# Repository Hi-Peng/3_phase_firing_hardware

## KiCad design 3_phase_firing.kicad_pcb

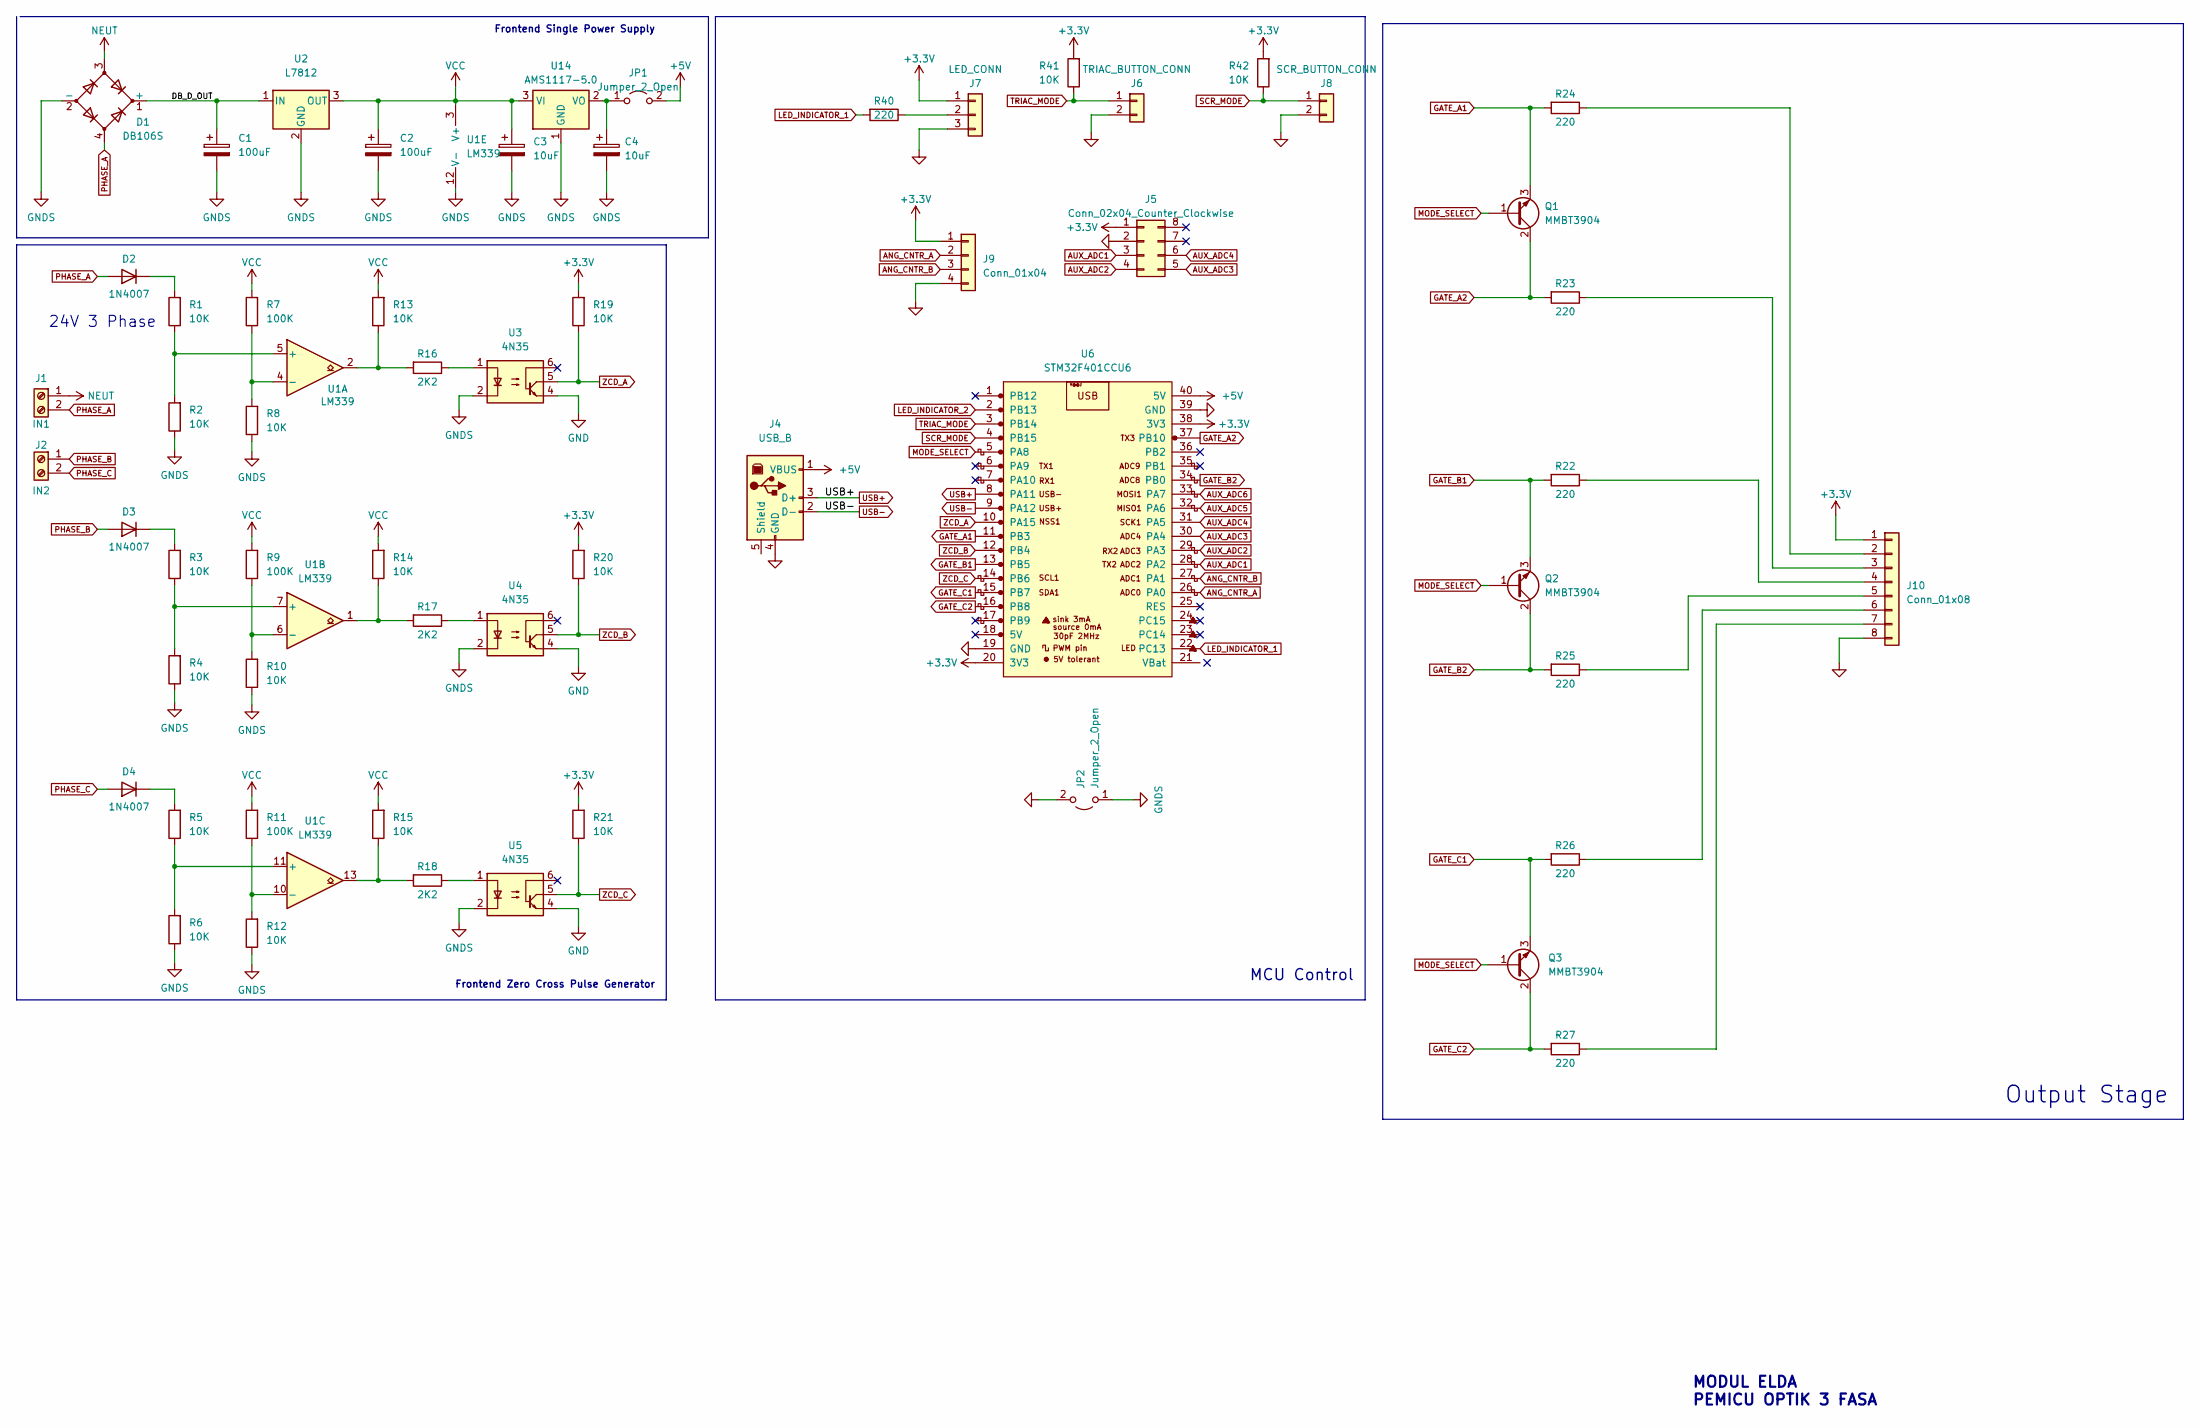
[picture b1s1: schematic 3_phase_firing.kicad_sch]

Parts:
C1, C2: 100uF; CP_Elec_6.3x7.7
C3, C4: 10uF; CP_Elec_6.3x7.7
D1: DB106S; Diode_Bridge_OnSemi_SDIP-4L
D2, D3, D4: 1N4007; D_SMA_Handsoldering
J1: IN1; TerminalBlock_bornier-2_P5.08mm
J2: IN2; TerminalBlock_bornier-2_P5.08mm
J4: USB_B; USB_B_OST_USB-B1HSxx_Horizontal
J5: Conn_02x04_Counter_Clockwise; PinHeader_2x04_P2.54mm_Vertical
J6: TRIAC_BUTTON_CONN; JST_XH_B2B-XH-A_1x02_P2.50mm_Vertical
J7: LED_CONN; JST_XH_B3B-XH-A_1x03_P2.50mm_Vertical
J8: SCR_BUTTON_CONN; JST_XH_B2B-XH-A_1x02_P2.50mm_Vertical
J9: Conn_01x04; JST_XH_B4B-XH-A_1x04_P2.50mm_Vertical
J10: Conn_01x08; JST_XH_B8B-XH-A_1x08_P2.50mm_Vertical
JP1, JP2: Jumper_2_Open; PinHeader_1x02_P2.54mm_Vertical
Q1, Q2, Q3: MMBT3904; SOT-23
R1, R2, R3, R4, R5, R6, R8, R10, R12, R13, R14, R15, R19, R20, R21, R41, R42: 10K; R_0805_2012Metric
R7, R9, R11: 100K; R_0805_2012Metric
R16, R17, R18: 2K2; R_0805_2012Metric
R22, R23, R24, R25, R26, R27: 220; R_0805_2012Metric
R40: 220; R_1206_3216Metric_Pad1.30x1.75mm_HandSolder
U1: LM339; SOIC-14_3.9x8.7mm_P1.27mm
U2: L7812; TO-263-2
U3, U4, U5: 4N35; DIP-6_W8.89mm_SMDSocket_LongPads
U6: STM32F401CCU6; YAAJ_WeAct_BlackPill_2
U14: AMS1117-5.0; SOT-223-3_TabPin2

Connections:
+3.3V: J5.1, J7.1, J9.1, J10.1, R19.2, R20.2, R21.2, R41.2, R42.2, U6.20 (3V3), U6.38 (3V3)
+5V: J4.1 (VBUS), JP1.2 (B), U6.40 (5V)
/DB_D_OUT: C1.1, D1.1 (+), U2.1 (IN)
ANG_CNTR_A: J9.2, U6.26 (PA0)
ANG_CNTR_B: J9.3, U6.27 (PA1)
AUX_ADC1: J5.3, U6.28 (PA2)
AUX_ADC2: J5.4, U6.29 (PA3)
AUX_ADC3: J5.5, U6.30 (PA4)
AUX_ADC4: J5.6, U6.31 (PA5)
AUX_ADC5: U6.32 (PA6)
AUX_ADC6: U6.33 (PA7)
GATE_A1: Q1.3 (E), R24.2, U6.11 (PB3)
GATE_A2: Q1.2 (C), R23.2, U6.37 (PB10)
GATE_B1: Q2.3 (E), R22.2, U6.13 (PB5)
GATE_B2: Q2.2 (C), R25.2, U6.34 (PB0)
GATE_C1: Q3.3 (E), R26.2, U6.15 (PB7)
GATE_C2: Q3.2 (C), R27.2, U6.16 (PB8)
GND: J4.4 (GND), J5.2, J6.2, J7.3, J8.2, J9.4, J10.8, JP2.2 (B), U3.4, U4.4, U5.4, U6.19 (GND), U6.39 (GND)
GNDS: C1.2, C2.2, C3.2, C4.2, D1.2 (-), JP2.1 (A), R2.1, R4.1, R6.1, R8.1, R10.1, R12.1, U1.12 (V-), U2.2 (GND), U3.2, U4.2, U5.2, U14.1 (GND)
LED_INDICATOR_1: R40.2, U6.22 (PC13)
LED_INDICATOR_2: U6.2 (PB13)
MODE_SELECT: Q1.1 (B), Q2.1 (B), Q3.1 (B), U6.5 (PA8)
NEUT: D1.3, J1.1
unnamed: D2.1 (K), R1.2
unnamed: D3.1 (K), R3.2
unnamed: D4.1 (K), R5.2
unnamed: J7.2, R40.1
unnamed: J10.2, R24.1
unnamed: J10.3, R23.1
unnamed: J10.4, R22.1
unnamed: J10.5, R25.1
unnamed: J10.6, R26.1
unnamed: J10.7, R27.1
unnamed: C4.1, JP1.1 (A), U14.2 (VO)
unnamed: R13.1, R16.2, U1.2
unnamed: R14.1, R17.2, U1.1
unnamed: R15.1, R18.2, U1.13
unnamed: R16.1, U3.1
unnamed: R17.1, U4.1
unnamed: R18.1, U5.1
unnamed: R1.1, R2.2, U1.5 (+)
unnamed: R7.1, R8.2, U1.4 (-)
unnamed: R3.1, R4.2, U1.7 (+)
unnamed: R9.1, R10.2, U1.6 (-)
unnamed: R5.1, R6.2, U1.11 (+)
unnamed: R11.1, R12.2, U1.10 (-)
PHASE_A: D1.4, D2.2 (A), J1.2
PHASE_B: D3.2 (A), J2.1
PHASE_C: D4.2 (A), J2.2
SCR_MODE: J8.1, R42.1, U6.4 (PB15)
TRIAC_MODE: J6.1, R41.1, U6.3 (PB14)
USB+: J4.3 (D+), U6.8 (PA11)
USB-: J4.2 (D-), U6.9 (PA12)
VCC: C2.1, C3.1, R7.2, R9.2, R11.2, R13.2, R14.2, R15.2, U1.3 (V+), U2.3 (OUT), U14.3 (VI)
ZCD_A: R19.1, U3.5, U6.10 (PA15)
ZCD_B: R20.1, U4.5, U6.12 (PB4)
ZCD_C: R21.1, U5.5, U6.14 (PB6)

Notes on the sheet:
MODUL ELDA PEMICU OPTIK 3 FASA
Frontend Zero Cross Pulse Generator
MCU Control
Frontend Single Power Supply
24V 3 Phase
Output Stage

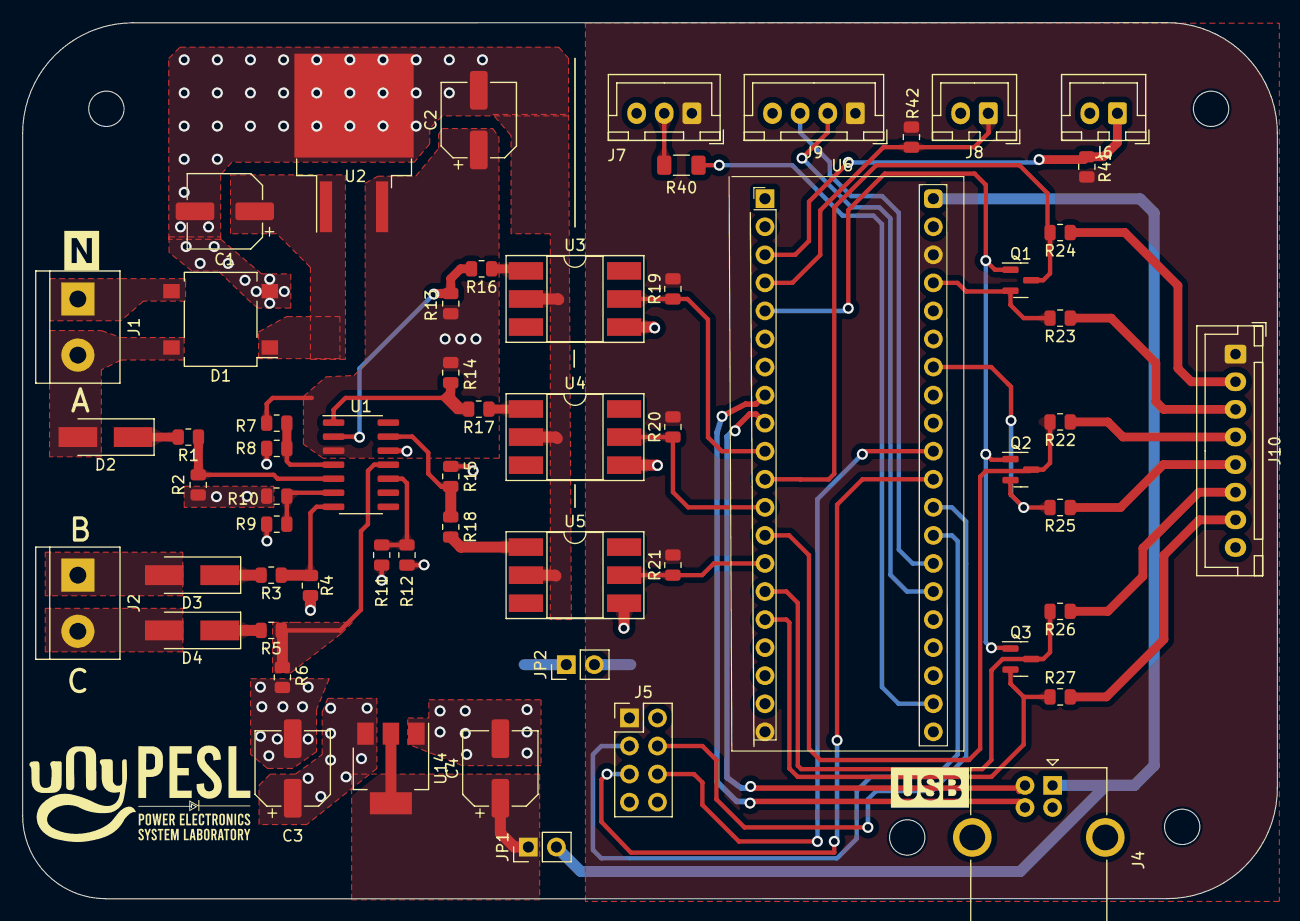
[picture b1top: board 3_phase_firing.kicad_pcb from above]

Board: 2 copper layers, 113.6 x 79.3 mm, 61 parts (0 on the bottom side), 54 nets.

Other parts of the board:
kibuzzard-63D8BD9F: G***; kibuzzard-63D8BD9F
kibuzzard-63D55C26: G***; kibuzzard-63D55C26

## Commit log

2023-01-28 fixing schematics and pcb layout, adding usb and knob control
2023-02-14 done with all revision
2023-03-05 fixing psu issue and 3d libs update
2023-04-08 fixing unconnected bootstrap
